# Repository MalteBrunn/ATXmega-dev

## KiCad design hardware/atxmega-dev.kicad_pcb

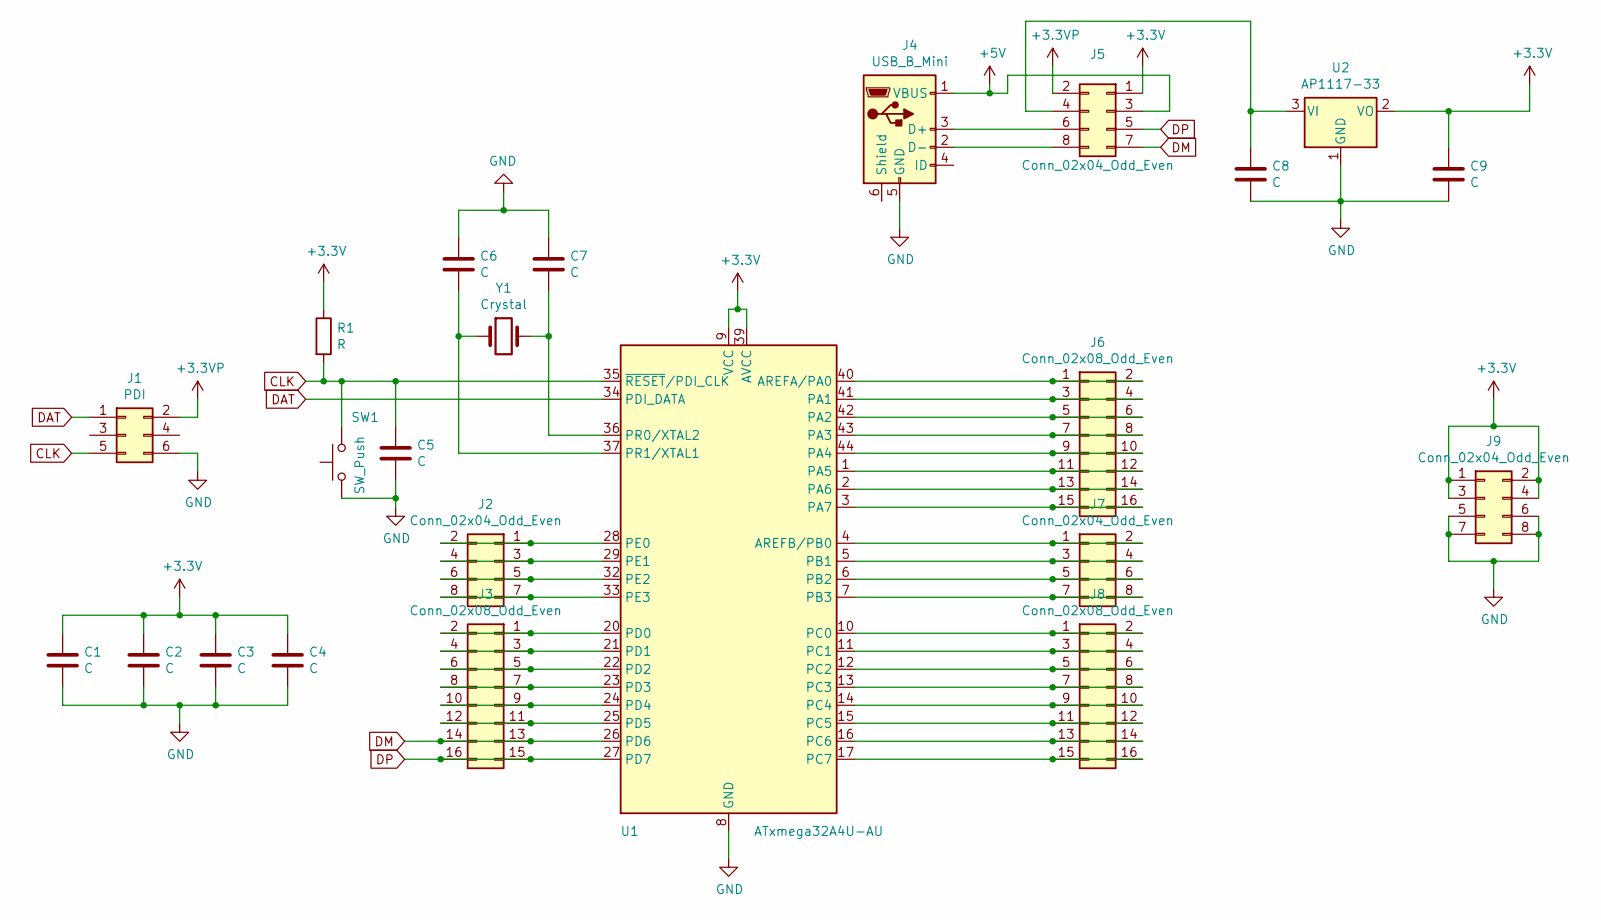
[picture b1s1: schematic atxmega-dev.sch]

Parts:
C1, C2, C3, C4, C5, C6, C7, C8, C9: C; C_0805_2012Metric_Pad1.15x1.40mm_HandSolder
J1: PDI; IDC-Header_2x03_P2.54mm_Vertical
J2, J5, J7, J9: Conn_02x04_Odd_Even; PinHeader_2x04_P2.54mm_Vertical
J3, J6, J8: Conn_02x08_Odd_Even; PinHeader_2x08_P2.54mm_Vertical
J4: USB_B_Mini; USB_Mini-B_Lumberg_2486_01_Horizontal
R1: R; R_0805_2012Metric_Pad1.15x1.40mm_HandSolder
SW1: SW_Push; SW_SPST_B3S-1000
U1: ATxmega32A4U-AU; TQFP-44_10x10mm_P0.8mm_Handsoldering
U2: AP1117-33; SOT-223-3_TabPin2
Y1: Crystal; Crystal_HC49-U_Vertical

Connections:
+3.3VP: J1.2, J5.2
+3V3: C1.1, C2.1, C3.1, C4.1, C9.1, J5.1, J9.1, J9.2, J9.3, J9.4, R1.1, U1.9 (VCC), U1.19 (VCC), U1.31 (VCC), U1.39 (AVCC), U2.2 (VO)
+5V: J4.1 (VBUS), J5.3
CLK: C5.1, J1.5, R1.2, SW1.2, U1.35 (~RESET~/PDI_CLK); also elsewhere on the board
DAT: J1.1, U1.34 (PDI_DATA)
DM: J3.13, J3.14, J5.7, U1.26 (PD6)
DP: J3.15, J3.16, J5.5, U1.27 (PD7)
GND: C1.2, C2.2, C3.2, C4.2, C5.2, C6.1, C7.1, C8.2, C9.2, J1.6, J4.5 (GND), J9.5, J9.6, J9.7, J9.8, SW1.1, U1.8 (GND), U1.18 (GND), U1.30 (GND), U1.38 (GND), U2.1 (GND); also elsewhere on the board
unnamed: C6.2, U1.37 (PR1/XTAL1), Y1.1
unnamed: C7.2, U1.36 (PR0/XTAL2), Y1.2
unnamed: C8.1, J5.4, U2.3 (VI)
unnamed: J2.1, J2.2, U1.28 (PE0)
unnamed: J2.3, J2.4, U1.29 (PE1)
unnamed: J2.5, J2.6, U1.32 (PE2)
unnamed: J2.7, J2.8, U1.33 (PE3)
unnamed: J3.1, J3.2, U1.20 (PD0)
unnamed: J3.3, J3.4, U1.21 (PD1)
unnamed: J3.5, J3.6, U1.22 (PD2)
unnamed: J3.7, J3.8, U1.23 (PD3)
unnamed: J3.9, J3.10, U1.24 (PD4)
unnamed: J3.11, J3.12, U1.25 (PD5)
unnamed: J4.2 (D-), J5.8
unnamed: J4.3 (D+), J5.6
unnamed: J6.1, J6.2, U1.40 (AREFA/PA0)
unnamed: J6.3, J6.4, U1.41 (PA1)
unnamed: J6.5, J6.6, U1.42 (PA2)
unnamed: J6.7, J6.8, U1.43 (PA3)
unnamed: J6.9, J6.10, U1.44 (PA4)
unnamed: J6.11, J6.12, U1.1 (PA5)
unnamed: J6.13, J6.14, U1.2 (PA6)
unnamed: J6.15, J6.16, U1.3 (PA7)
unnamed: J7.1, J7.2, U1.4 (AREFB/PB0)
unnamed: J7.3, J7.4, U1.5 (PB1)
unnamed: J7.5, J7.6, U1.6 (PB2)
unnamed: J7.7, J7.8, U1.7 (PB3)
unnamed: J8.1, J8.2, U1.10 (PC0)
unnamed: J8.3, J8.4, U1.11 (PC1)
unnamed: J8.5, J8.6, U1.12 (PC2)
unnamed: J8.7, J8.8, U1.13 (PC3)
unnamed: J8.9, J8.10, U1.14 (PC4)
unnamed: J8.11, J8.12, U1.15 (PC5)
unnamed: J8.13, J8.14, U1.16 (PC6)
unnamed: J8.15, J8.16, U1.17 (PC7)

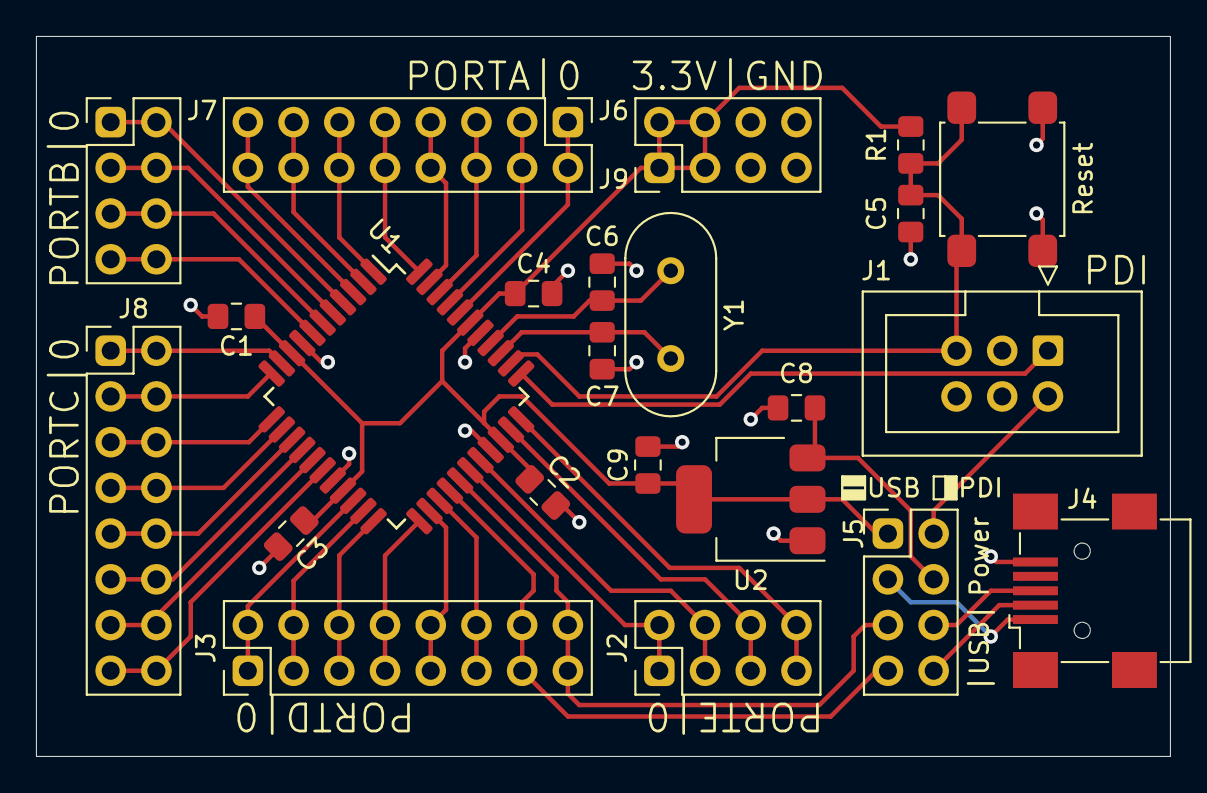
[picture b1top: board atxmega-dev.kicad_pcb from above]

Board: 2 copper layers, 63.0 x 40.0 mm, 23 parts (0 on the bottom side), 43 nets.

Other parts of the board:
Reset: SW_Push; SW_SPST_B3S-1000

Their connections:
CLK: Reset.2; also elsewhere on the board
GND: Reset.1; also elsewhere on the board

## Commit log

2021-01-17 xmega32a4u test and board
